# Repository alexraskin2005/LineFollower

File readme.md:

# LineFollower

Line follower project op HoGent

## specifications

microcontroller: ESP32

motors: N20 6V 1000RPM

h-bridge: DRV8833

sensors: QTR-8A (fake version)

batteries: lipo 2s 1000mah 20C

wireless communication: ESP32

distance sensor - motors: +-9cm

speed: 0.66 m/s

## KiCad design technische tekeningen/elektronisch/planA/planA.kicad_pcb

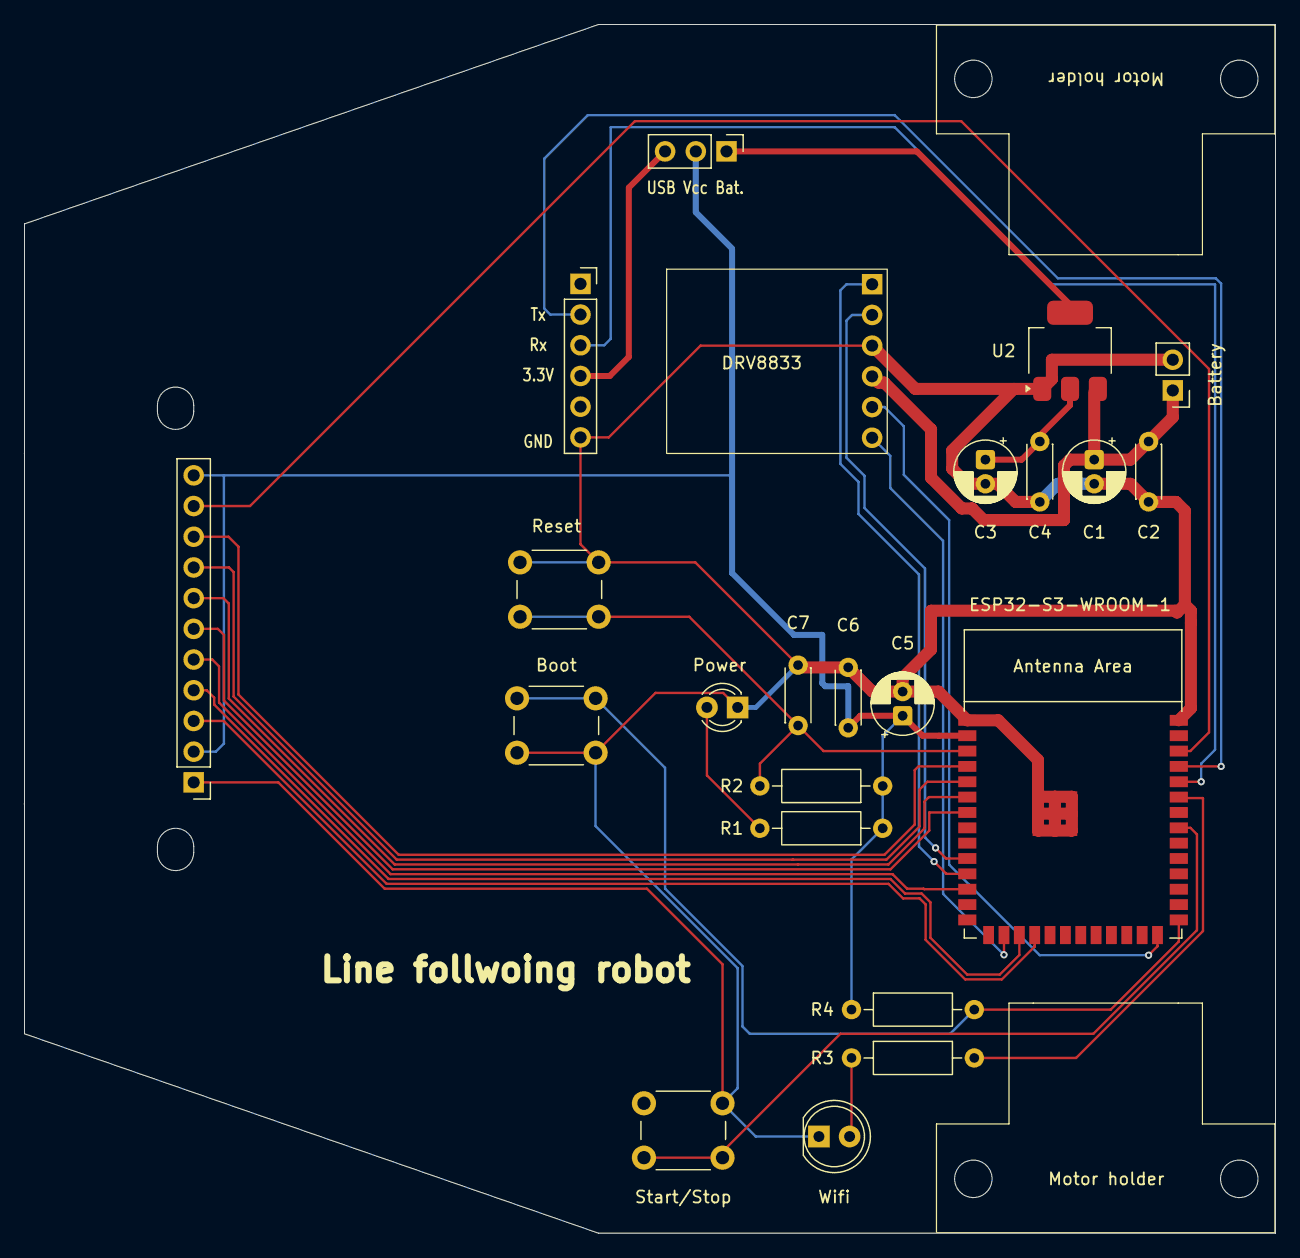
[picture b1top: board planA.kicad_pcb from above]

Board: 2 copper layers, 103.5 x 100.0 mm, 25 parts (0 on the bottom side), 25 nets.

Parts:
Battery: Battery; PinHeader_1x02_P2.54mm_Vertical
Boot: boot; SW_PUSH_6mm_H4.3mm
C1, C3, C5: 10uF; CP_Radial_D5.0mm_P2.00mm
C2, C4, C6, C7: 0u1F; C_Disc_D4.3mm_W1.9mm_P5.00mm
DRV8833: DRV8833 module; DRV8833_Module_1x06_P2,54mm
J1: Connector_usb_to_ttl; PinSocket_1x06_P2.54mm_Vertical
M1, M2: Motor_DC; motor holder
Power: PWR; LED_D3.0mm
R1, R3: 150(220); R_Axial_DIN0207_L6.3mm_D2.5mm_P10.16mm_Horizontal
R2, R4: 10k; R_Axial_DIN0207_L6.3mm_D2.5mm_P10.16mm_Horizontal
Reset: reset; SW_PUSH_6mm_H4.3mm
SN1: 8 channel ir sensor; 8channel_ir_sensor_1x11_P2.54mm
Start/Stop: start/stop; SW_PUSH_6mm_H4.3mm
U1: ESP32-S3-WROOM-1
U2: AMS1117-3.3; SOT-223-3_TabPin2
USB Vcc Bat.: jumper esp voltage; PinHeader_1x03_P2.54mm_Vertical
Wifi: Wifi; LED_D5.0mm

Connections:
BT_7.4V: Battery.1 (+), C1.1, C2.1, DRV8833.4 (VCC), U2.3 (VI)
ESP_3.3V: C5.1, C6.1, R1.1, R2.1, R4.1, SN1.2 (IR), SN1.11 (VCC), U1.2 (3V3), USB Vcc Bat..2
GND: Battery.2 (-), Boot.2, C1.2, C2.2, C3.2, C4.2, C5.2, C6.2, C7.2, DRV8833.3 (GND), J1.6 (GND), Power.1 (K), Reset.1, SN1.1 (GND), Start/Stop.1, U1.1 (GND), U1.40 (GND), U1.41 (GND), U2.1 (GND), Wifi.1 (K)
GPIO17: DRV8833.2 (IN3), U1.10 (GPIO17/U1TXD/ADC2_CH6)
GPIO18: DRV8833.1 (IN4), U1.11 (GPIO18/U1RXD/ADC2_CH7/CLK_OUT3)
GPIO45: DRV8833.5 (IN2), U1.26 (GPIO45)
GPIO46: DRV8833.6 (IN1), U1.16 (GPIO46)
unnamed: Power.2 (A), R1.2
unnamed: R3.1, Wifi.2 (A)
unnamed: J1.4 (VCC), USB Vcc Bat..3
unnamed: SN1.3 (D1), U1.18 (GPIO10/TOUCH10/ADC1_CH9/FSPICS0/FSPIIO4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)
unnamed: SN1.4 (D2), U1.17 (GPIO9/TOUCH9/ADC1_CH8/FSPIHD/SUBSPIHD)
unnamed: SN1.5 (D3), U1.12 (GPIO8/TOUCH8/ADC1_CH7/SUBSPICS1)
unnamed: SN1.6 (D4), U1.7 (GPIO7/TOUCH7/ADC1_CH6)
unnamed: SN1.7 (D5), U1.6 (GPIO6/TOUCH6/ADC1_CH5)
unnamed: SN1.8 (D6), U1.5 (GPIO5/TOUCH5/ADC1_CH4)
unnamed: SN1.9 (D7), U1.4 (GPIO4/TOUCH4/ADC1_CH3)
unnamed: SN1.10 (D8), U1.38 (GPIO2/TOUCH2/ADC1_CH1)
unnamed: C7.1, R2.2, Reset.2, U1.3 (EN)
unnamed: Boot.1, R4.2, U1.27 (GPIO0/BOOT)
unnamed: Start/Stop.2, U1.33 (MTDO/GPIO40/CLK_OUT2)
unnamed: R3.2, U1.35 (MTMS/GPIO42)
RXD0: J1.3 (TX), U1.36 (U0RXD/GPIO44/CLK_OUT2)
TXD0: J1.2 (RX), U1.37 (U0TXD/GPIO43/CLK_OUT1)
VCC_3.3V: C3.1, C4.1, U2.2 (VO), USB Vcc Bat..1

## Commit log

2025-10-09 Revert "Update datasheets.md"
    This reverts commit 082e1b59164668246b098eba71af7abccb822a06.
2025-10-10 Create planA
2025-10-10 Rename planA to planA.md
2025-10-17 electrische tekeningen
2025-10-17 code
2025-10-17 modified version of code ment for proof of concept
2025-10-17 gui3 and module1 fix
2025-10-17 code genminimalliseerd voor proof of concept
2025-10-17 planB elek to pdf
2025-10-17 button added
2025-10-30 begin cad ontwerp
2025-10-30 begin pcb
2025-12-04 Update distance sensor and speed details in readme
2025-12-04 Update image in readme with new screenshot
2025-12-04 Rename Screenshot 2025-11-26 145458.png to planA.png
